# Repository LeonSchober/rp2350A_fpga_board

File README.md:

# rp2350A_fpga_board
rp2350A_fpga_board

RP2350 & iCE40 FPGA Development Board
This repository contains the hardware design files for a compact, high-performance development board combining the Raspberry Pi RP2350 MCU and the Lattice iCE40UP5K FPGA. This dual-chip architecture bridges the gap between flexible software execution and high-speed, parallel hardware acceleration, making it ideal for edge-computing, custom digital logic, and advanced interfacing projects.

Technical Specifications
Core Components
Microcontroller: Raspberry Pi RP2350A (ARM Cortex-M33 / Hazard3 RISC-V)

FPGA: Lattice iCE40 UltraPlus (iCE40UP5K-SG48ITR) – 5280 LUTs, 120 Kbit EBR, 1024 Kbit Single Port RAM

Storage: Winbond W25Q128JVS (128 Mbit / 16 MB QSPI Flash) shared/accessible for configuration

Power & Connectivity
Interface: USB Type-C for power, programming, and debugging

Power Management: Dual AP2112K LDO regulators providing stable 3.3V and 1.2V rails; onboard filtering networks for analog and PLL domains

User Interfacing: * Dedicated BOOT and RUN (Reset) buttons for the MCU

User-programmable button (Push-IO4) and status LEDs (Done, RGB)

High-density dual-row breadboard-compatible pin headers exposing GPIOs from both MCU and FPGA

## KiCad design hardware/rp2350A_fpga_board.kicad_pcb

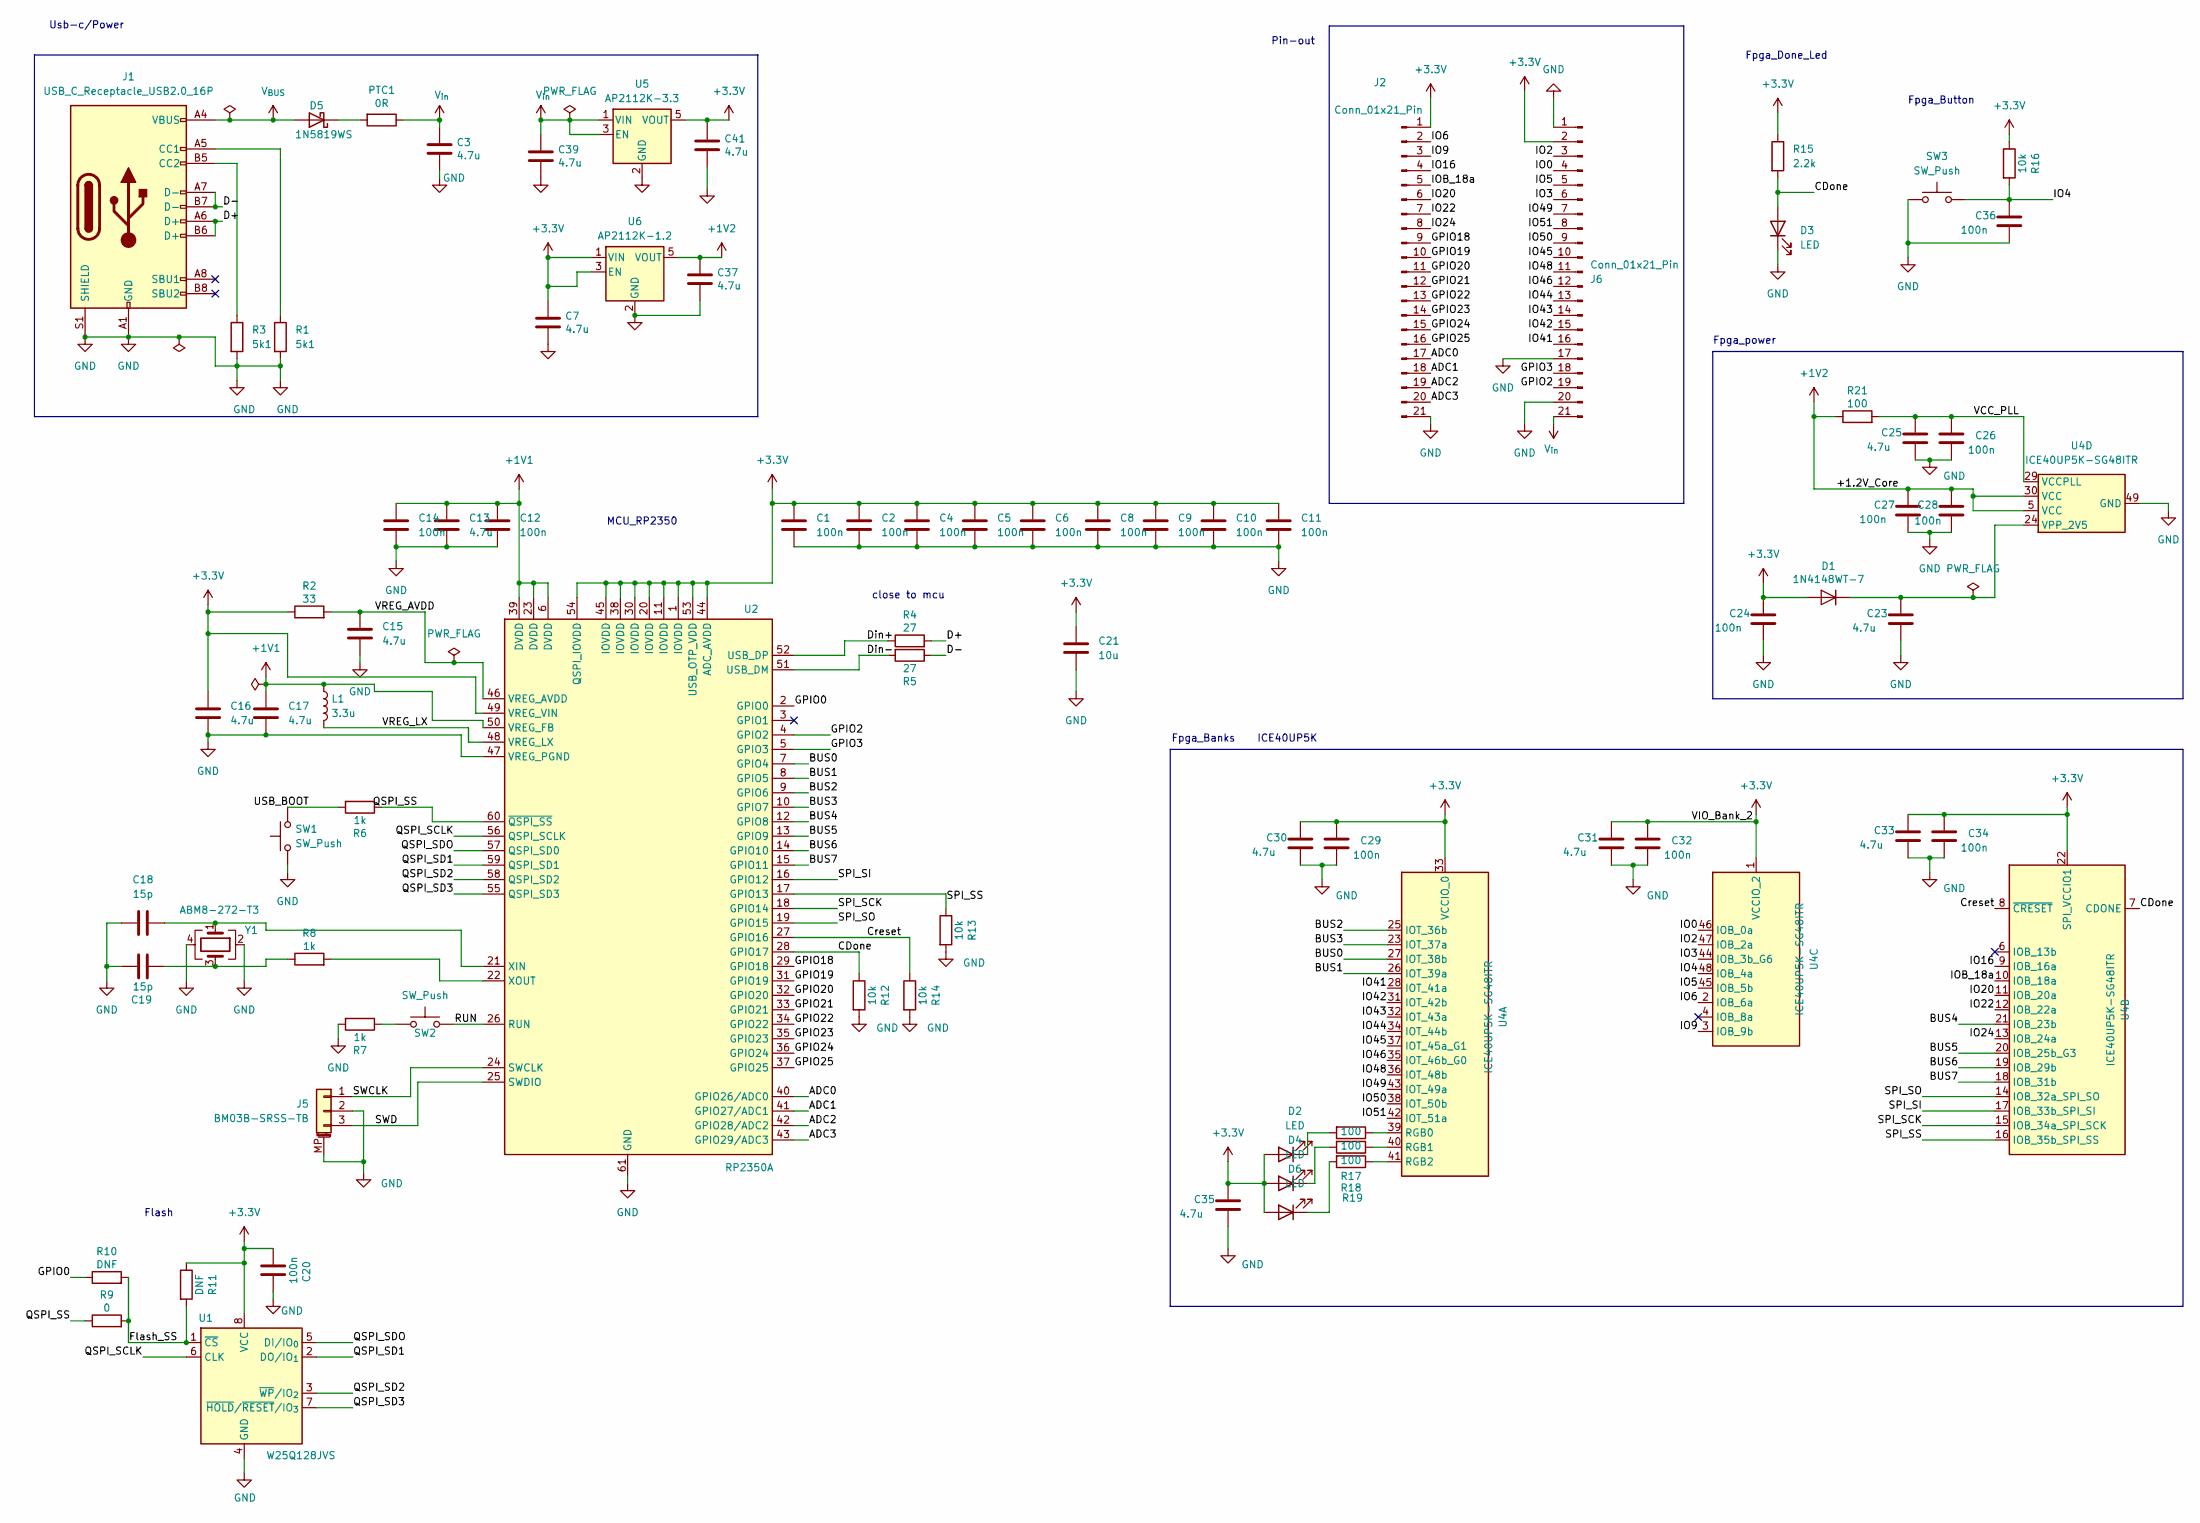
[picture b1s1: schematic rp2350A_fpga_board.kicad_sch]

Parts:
C1, C2, C4, C5, C6, C8, C9, C10, C11, C12, C14, C20, C24, C26, C27, C28, C29, C32, C34, C36: 100n; C_0603_1608Metric
C3, C7, C37, C39, C41: 4.7u; C_0603_1608Metric; MPN GRM155R60J475ME87D
C13, C15, C16, C17, C23, C25, C30, C31, C33, C35: 4.7u; C_0603_1608Metric
C18, C19: 15p; C_0603_1608Metric
C21: 10u; C_0805_2012Metric
D1: 1N4148WT-7; D_SOD-523; MPN 1N4148WT-7
D2, D3, D4, D6: LED; LED_0603_1608Metric
D5: 1N5819WS; D_SOD-323; MPN 1N5819WS
J1: USB_C_Receptacle_USB2.0_16P; USB_C_Receptacle_G-Switch_GT-USB-7010ASV
J2, J6: Conn_01x21_Pin; PinHeader_1x21_P2.54mm_Vertical
J5: BM03B-SRSS-TB; JST_SH_BM03B-SRSS-TB_1x03-1MP_P1.00mm_Vertical; MPN BM03B-SRSS-TB
L1: 3.3u; L_1210_3225Metric
PTC1: 0R; R_0603_1608Metric; MPN MF-FSMF035X-2
R1, R3: 5k1; R_0603_1608Metric
R2: 33; R_0603_1608Metric
R4, R5: 27; R_0603_1608Metric
R6, R7, R8: 1k; R_0603_1608Metric
R9: 0; R_0603_1608Metric
R10, R11: DNF; R_0603_1608Metric
R12, R13, R14, R16: 10k; R_0603_1608Metric
R15: 2.2k; R_0603_1608Metric
R17, R18, R19, R21: 100; R_0603_1608Metric
SW1, SW2, SW3: SW_Push; SW_SPST_B3U-1000P
U1: W25Q128JVS; SOIC-8_5.3x5.3mm_P1.27mm
U2: RP2350A; QFN-60-1EP_7x7mm_P0.4mm_EP3.4x3.4mm
U4: ICE40UP5K-SG48ITR; QFN-48-1EP_7x7mm_P0.5mm_EP5.6x5.6mm
U5: AP2112K-3.3; SOT-23-5
U6: AP2112K-1.2; SOT-23-5
Y1: ABM8-272-T3; Crystal_SMD_3225-4Pin_3.2x2.5mm; MPN ABM8-272-T3

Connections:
+1V1: C12.1, C13.1, C14.1, C17.1, L1.1, U2.6 (DVDD), U2.23 (DVDD), U2.39 (DVDD), U2.50 (VREG_FB)
+1V2: C27.1, C28.1, C37.1, R21.1, U4.5 (VCC), U4.30 (VCC), U6.5 (VOUT)
+3.3V: C1.1, C2.1, C4.1, C5.1, C6.1, C7.1, C8.1, C9.1, C10.1, C11.1, C16.1, C20.2, C21.1, C24.1, C29.1, C30.1, C31.1, C32.1, C33.1, C34.1, C35.1, C41.1, D1.2 (A), D2.2 (A), D4.2 (A), D6.2 (A), J2.1, J6.2, R2.1, R11.1, R15.1, R16.1, U1.8 (VCC), U2.1 (IOVDD), U2.11 (IOVDD), U2.20 (IOVDD), U2.30 (IOVDD), U2.38 (IOVDD), U2.44 (ADC_AVDD), U2.45 (IOVDD), U2.49 (VREG_VIN), U2.53 (USB_OTP_VDD), U2.54 (QSPI_IOVDD), U4.1 (VCCIO_2), U4.22 (SPI_VCCIO1), U4.33 (VCCIO_0), U5.5 (VOUT), U6.1 (VIN), U6.3 (EN)
/ADC0: J2.17, U2.40 (GPIO26/ADC0)
/ADC1: J2.18, U2.41 (GPIO27/ADC1)
/ADC2: J2.19, U2.42 (GPIO28/ADC2)
/ADC3: J2.20, U2.43 (GPIO29/ADC3)
/BUS0: U2.7 (GPIO4), U4.27 (IOT_38b)
/BUS1: U2.8 (GPIO5), U4.26 (IOT_39a)
/BUS2: U2.9 (GPIO6), U4.25 (IOT_36b)
/BUS3: U2.10 (GPIO7), U4.23 (IOT_37a)
/BUS4: U2.12 (GPIO8), U4.21 (IOB_23b)
/BUS5: U2.13 (GPIO9), U4.20 (IOB_25b_G3)
/BUS6: U2.14 (GPIO10), U4.19 (IOB_29b)
/BUS7: U2.15 (GPIO11), U4.18 (IOB_31b)
/CDone: D3.2 (A), R12.1, R15.2, U2.28 (GPIO17), U4.7 (CDONE)
/Creset: R14.1, U2.27 (GPIO16), U4.8 (~CRESET)
/D+: J1.A6 (D+), J1.B6 (D+), R4.2
/D-: J1.A7 (D-), J1.B7 (D-), R5.1
/Din+: R4.1, U2.52 (USB_DP)
/Din-: R5.2, U2.51 (USB_DM)
/Flash_SS: R9.2, R10.2, R11.2, U1.1 (~CS)
/GPIO0: R10.1, U2.2 (GPIO0)
/GPIO2: J6.19, U2.4 (GPIO2)
/GPIO3: J6.18, U2.5 (GPIO3)
/GPIO18: J2.9, U2.29 (GPIO18)
/GPIO19: J2.10, U2.31 (GPIO19)
/GPIO20: J2.11, U2.32 (GPIO20)
/GPIO21: J2.12, U2.33 (GPIO21)
/GPIO22: J2.13, U2.34 (GPIO22)
/GPIO23: J2.14, U2.35 (GPIO23)
/GPIO24: J2.15, U2.36 (GPIO24)
/GPIO25: J2.16, U2.37 (GPIO25)
/IO0: J6.4, U4.46 (IOB_0a)
/IO2: J6.3, U4.47 (IOB_2a)
/IO3: J6.6, U4.44 (IOB_3b_G6)
/IO4: C36.1, R16.2, SW3.2, U4.48 (IOB_4a)
/IO5: J6.5, U4.45 (IOB_5b)
/IO6: J2.2, U4.2 (IOB_6a)
/IO9: J2.3, U4.3 (IOB_9b)
/IO16: J2.4, U4.9 (IOB_16a)
/IO20: J2.6, U4.11 (IOB_20a)
/IO22: J2.7, U4.12 (IOB_22a)
/IO24: J2.8, U4.13 (IOB_24a)
/IO41: J6.16, U4.28 (IOT_41a)
/IO42: J6.15, U4.31 (IOT_42b)
/IO43: J6.14, U4.32 (IOT_43a)
/IO44: J6.13, U4.34 (IOT_44b)
/IO45: J6.10, U4.37 (IOT_45a_G1)
/IO46: J6.12, U4.35 (IOT_46b_G0)
/IO48: J6.11, U4.36 (IOT_48b)
/IO49: J6.7, U4.43 (IOT_49a)
/IO50: J6.9, U4.38 (IOT_50b)
/IO51: J6.8, U4.42 (IOT_51a)
/IOB_18a: J2.5, U4.10 (IOB_18a)
/QSPI_SCLK: U1.6 (CLK), U2.56 (QSPI_SCLK)
/QSPI_SD1: U1.2 (DO/IO_{1}), U2.59 (QSPI_SD1)
/QSPI_SD2: U1.3 (~WP/IO_{2}), U2.58 (QSPI_SD2)
/QSPI_SD3: U1.7 (~HOLD/~RESET/IO_{3}), U2.55 (QSPI_SD3)
/QSPI_SDO: U1.5 (DI/IO_{0}), U2.57 (QSPI_SD0)
/QSPI_SS: R6.1, R9.1, U2.60 (~QSPI_SS)
/RUN: SW2.2, U2.26 (RUN)
/SPI_SCK: U2.18 (GPIO14), U4.15 (IOB_34a_SPI_SCK)
/SPI_SI: U2.16 (GPIO12), U4.17 (IOB_33b_SPI_SI)
/SPI_SO: U2.19 (GPIO15), U4.14 (IOB_32a_SPI_SO)
/SPI_SS: R13.1, U2.17 (GPIO13), U4.16 (IOB_35b_SPI_SS)
/SWCLK: J5.1, U2.24 (SWCLK)
/SWD: J5.3, U2.25 (SWDIO)
/USB_BOOT: R6.2, SW1.2
/VCC_PLL: C25.1, C26.1, R21.2, U4.29 (VCCPLL)
/VREG_AVDD: C15.1, R2.2, U2.46 (VREG_AVDD)
/VREG_LX: L1.2, U2.48 (VREG_LX)
GND: C1.2, C2.2, C3.2, C4.2, C5.2, C6.2, C7.2, C8.2, C9.2, C10.2, C11.2, C12.2, C13.2, C14.2, C15.2, C16.2, C17.2, C18.1, C19.1, C20.1, C21.2, C23.2, C24.2, C25.2, C26.2, C27.2, C28.2, C29.2, C30.2, C31.2, C32.2, C33.2, C34.2, C35.2, C36.2, C37.2, C39.2, C41.2, D3.1 (K), J1.A1 (GND), J1.B1 (GND), J1.S1 (SHIELD), J2.21, J5.2, J5.MP (MountPin), J6.1, J6.17, J6.20, R1.2, R3.2, R7.2, R12.2, R13.2, R14.2, SW1.1, SW3.1, U1.4 (GND), U2.47 (VREG_PGND), U2.61 (GND), U4.49 (GND), U5.2 (GND), U6.2 (GND), Y1.2, Y1.4
unnamed: C19.2, R8.1, Y1.3
unnamed: C23.1, D1.1 (K), U4.24 (VPP_2V5)
unnamed: D2.1 (K), R17.2
unnamed: D4.1 (K), R18.2
unnamed: D5.1 (K), PTC1.2
unnamed: D6.1 (K), R19.2
unnamed: J1.A5 (CC1), R1.1
unnamed: J1.B5 (CC2), R3.1
unnamed: R7.1, SW2.1
unnamed: C18.2, U2.21 (XIN), Y1.1
unnamed: R8.2, U2.22 (XOUT)
unnamed: R17.1, U4.39 (RGB0)
unnamed: R18.1, U4.40 (RGB1)
unnamed: R19.1, U4.41 (RGB2)
V_{BUS}: D5.2 (A), J1.A4 (VBUS), J1.A9 (VBUS), J1.B4 (VBUS), J1.B9 (VBUS)
V_{in}: C3.1, C39.1, J6.21, PTC1.1, U5.1 (VIN), U5.3 (EN)

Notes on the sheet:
MCU_RP2350
ICE40UP5K
Usb-c/Power
Flash
Fpga_Done_Led
Fpga_power
Fpga_Banks
close to mcu
Pin-out
Fpga_Button

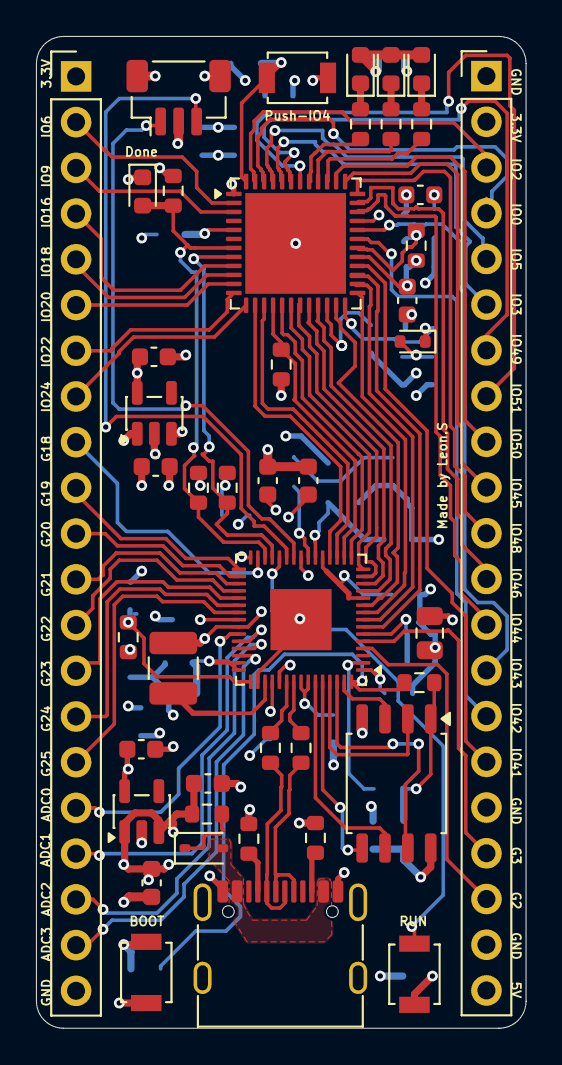
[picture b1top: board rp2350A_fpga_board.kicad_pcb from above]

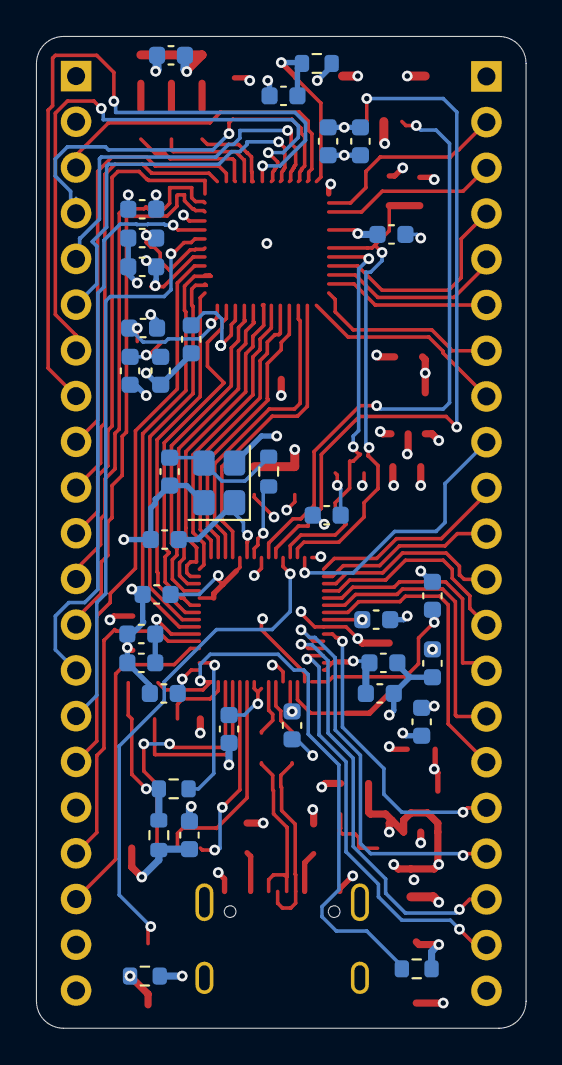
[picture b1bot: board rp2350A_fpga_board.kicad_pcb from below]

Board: 4 copper layers, 27.2 x 55.1 mm, 79 parts (35 on the bottom side), 89 nets.

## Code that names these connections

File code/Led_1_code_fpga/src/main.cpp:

// main.cpp – RP2350A programmiert ICE40UP5K per Slave-SPI

#include <Arduino.h>
#include <SPI.h>

#include "fpga_bitstream.h"
const uint8_t* bitfile     = (const uint8_t*)firmware_bin;
const uint32_t  bitfile_len = 12345;
// ── GPIO Pins (Exakt abgestimmt auf RP2350 Hardware-SPI1) ─────────────────
constexpr uint8_t PIN_FPGA_MISO   = 12;  // GPIO12 ← SPI1 RX (FPGA SO)
constexpr uint8_t PIN_FPGA_CS     = 13;  // GPIO13 → SPI1 CSn (FPGA SS)
constexpr uint8_t PIN_FPGA_SCK    = 14;  // GPIO14 → SPI1 SCK (FPGA CLK)
constexpr uint8_t PIN_FPGA_MOSI   = 15;  // GPIO15 → SPI1 TX (FPGA SI)
constexpr uint8_t PIN_FPGA_CRESET = 16;  // GPIO16 → Creset (Hardware-Reset)
constexpr uint8_t PIN_FPGA_CDONE  = 17;  // GPIO17 ← CDone (Status-Pin)

// ── SPI1 Pins setzen ──────────────────────────────────────────────────────
void spi_init_pins() {
    SPI1.setSCK(PIN_FPGA_SCK);
    SPI1.setTX(PIN_FPGA_MOSI);
    SPI1.setRX(PIN_FPGA_MISO);
    SPI1.setCS(PIN_FPGA_CS);
}

// ── Hilfsfunktionen ───────────────────────────────────────────────────────
void spi_send(const uint8_t* data, size_t len) {
    for (size_t i = 0; i < len; i++) {
        SPI1.transfer(data[i]);
    }
}

// ── Debug Info ────────────────────────────────────────────────────────────
void debug_info() {
    Serial.println("\n[DEBUG] System Info:");
    Serial.printf("  Freier Heap    : %d Bytes\n", rp2040.getFreeHeap());
    Serial.printf("  Bitfile Groesse: %lu Bytes\n", bitfile_len);
    Serial.printf("  Erste 4 Bytes  : 0x%02X 0x%02X 0x%02X 0x%02X\n",
                  bitfile[0], bitfile[1], bitfile[2], bitfile[3]);

    // Korrekter iCE40 Header-Check (iCE40 Bitstreams starten oft mit 0xFF)
    if (bitfile[0] == 0xFF) {
        Serial.println("  Bitfile Header: OK (Startet mit 0xFF Sync)");
    } else {
        Serial.println("  WARNUNG: Bitfile Header ungewöhnlich! Prüfe das raw-Format.");
    }

    Serial.printf("  CRESET : %s\n", digitalRead(PIN_FPGA_CRESET) ? "HIGH" : "LOW");
    Serial.printf("  CDONE  : %s\n", digitalRead(PIN_FPGA_CDONE)  ? "HIGH" : "LOW");
    Serial.println();
}

// ── FPGA Konfiguration ────────────────────────────────────────────────────
bool fpga_configure() {
    Serial.println("[FPGA] Starte Konfiguration...");

    // Schritt 1: Beide Pins definiert hochsetzen
    digitalWrite(PIN_FPGA_CS,     HIGH);
    digitalWrite(PIN_FPGA_CRESET, HIGH);
    delay(10);

    // Schritt 2: CS LOW, dann CRESET LOW (Zwingt iCE40 in den Slave-SPI Modus)
    digitalWrite(PIN_FPGA_CS,     LOW);
    delay(1);
    digitalWrite(PIN_FPGA_CRESET, LOW);
    delay(2);  // min. 200ns laut Datenblatt

    // Schritt 3: CRESET wieder HIGH (CS MUSS dabei zwingend LOW bleiben!)
    digitalWrite(PIN_FPGA_CRESET, HIGH);
    delay(5);  // iCE40 braucht bis zu 1.2ms zum Löschen des internen RAMs

    // Schritt 4: CDONE sollte jetzt LOW sein (Bereit für Daten)
    Serial.printf("  CDONE vor Konfig: %s (erwartet: LOW)\n",
                  digitalRead(PIN_FPGA_CDONE) ? "HIGH" : "LOW");

    // Schritt 5: 8 Dummy-Clocks mit CS HIGH
    digitalWrite(PIN_FPGA_CS, HIGH);
    delayMicroseconds(10);
    SPI1.transfer(0x00);  // 8 Clocks erzeugen
    delayMicroseconds(10);

    // Schritt 6: CS wieder LOW für die eigentliche Übertragung
    digitalWrite(PIN_FPGA_CS, LOW);
    delayMicroseconds(10);

    Serial.print("[FPGA] Sende Bitfile... ");
    Serial.flush();
    uint32_t t = millis();
    
    // Bitstream via SPI jagen
    spi_send(bitfile, bitfile_len);
    
    Serial.printf("fertig in %lums\n", millis() - t);

    // Schritt 7: CS wieder HIGH setzen
    digitalWrite(PIN_FPGA_CS, HIGH);

    // Schritt 8: Mindestens 49 zusätzliche Takte (Wake-up Clocks)
    // Damit taktet sich das FPGA aus dem Konfigurationsmodus in den User-Modus
    for (int i = 0; i < 7; i++) {
        SPI1.transfer(0x00);  // 7 * 8 = 56 Clocks
    }

    // Schritt 9: Kurze Pause und Erfolgskontrolle
    delay(100);
    bool success = (digitalRead(PIN_FPGA_CDONE) == HIGH);
    
    Serial.printf("  CDONE nach Konfig: %s\n", success ? "HIGH (ERFOLG!)" : "LOW (FEHLER)");
    Serial.println(success ? "[FPGA] Bootvorgang abgeschlossen!" : "[FPGA] Konfiguration fehlgeschlagen!");
    
    return success;
}

// ── Setup ─────────────────────────────────────────────────────────────────
void setup() {
    Serial.begin(115200);
    
    // Wartezeit beim Booten, damit du Zeit hast, den Serial Monitor zu öffnen
    delay(3000); 
    Serial.println("\n=== RP2350A TO iCE40 BOOTLOADER ===");
    Serial.flush();

    // GPIO Richtungen festlegen
    pinMode(PIN_FPGA_CS,     OUTPUT);
    pinMode(PIN_FPGA_CRESET, OUTPUT);
    pinMode(PIN_FPGA_CDONE,  INPUT);
    pinMode(PIN_FPGA_MISO, INPUT_PULLUP);

    // Grundzustand herstellen
    digitalWrite(PIN_FPGA_CS,     HIGH);
    digitalWrite(PIN_FPGA_CRESET, HIGH);

    // Zeige Debug-Werte im Terminal
    debug_info();

    // SPI1 initialisieren
    spi_init_pins();
    SPI1.begin();
    
    // Auf 5 MHz reduziert (5000000UL) für saubere Signale ohne Reflexionen
    SPI1.beginTransaction(SPISettings(5000000UL, MSBFIRST, SPI_MODE0));

    // FPGA programmieren
    if (!fpga_configure()) {
        SPI1.endTransaction();
        SPI1.end();
        Serial.println("[ERROR] Programmierung abgebrochen.");
        while (true) {
            Serial.println("[ERROR] Halted – Bitte Verkabelung und Pull-Ups prüfen.");
            delay(5000);
        }
    }

    // SPI nach erfolgreicher Programmierung freigeben
    SPI1.endTransaction();
    SPI1.end();

    Serial.println("[INFO] FPGA ist aktiv und läuft im User-Mode.");
}

// ── Loop ──────────────────────────────────────────────────────────────────
void loop() {
    static uint32_t last = 0;
    if (millis() - last >= 5000) {
        last = millis();
        bool cdone_status = digitalRead(PIN_FPGA_CDONE);
        Serial.printf("[STATUS] CDONE=%s  Uptime=%lus\n",
                      cdone_status ? "OK (HIGH)" : "FAIL (LOW)",
                      millis() / 1000UL);
    }
}

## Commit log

2026-06-30 Create da
2026-06-30 Create 1
2026-06-30 Rename Screenshot 2026-05-30 141004.png to front.png
2026-06-30 Rename Screenshot 2026-05-30 141039.png to back.png
2026-06-30 Create c
